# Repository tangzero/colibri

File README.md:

# colibri keyboard

## WIP ⚠️⚠️⚠️⚠️
this keyboard has not yet been tested

## Images

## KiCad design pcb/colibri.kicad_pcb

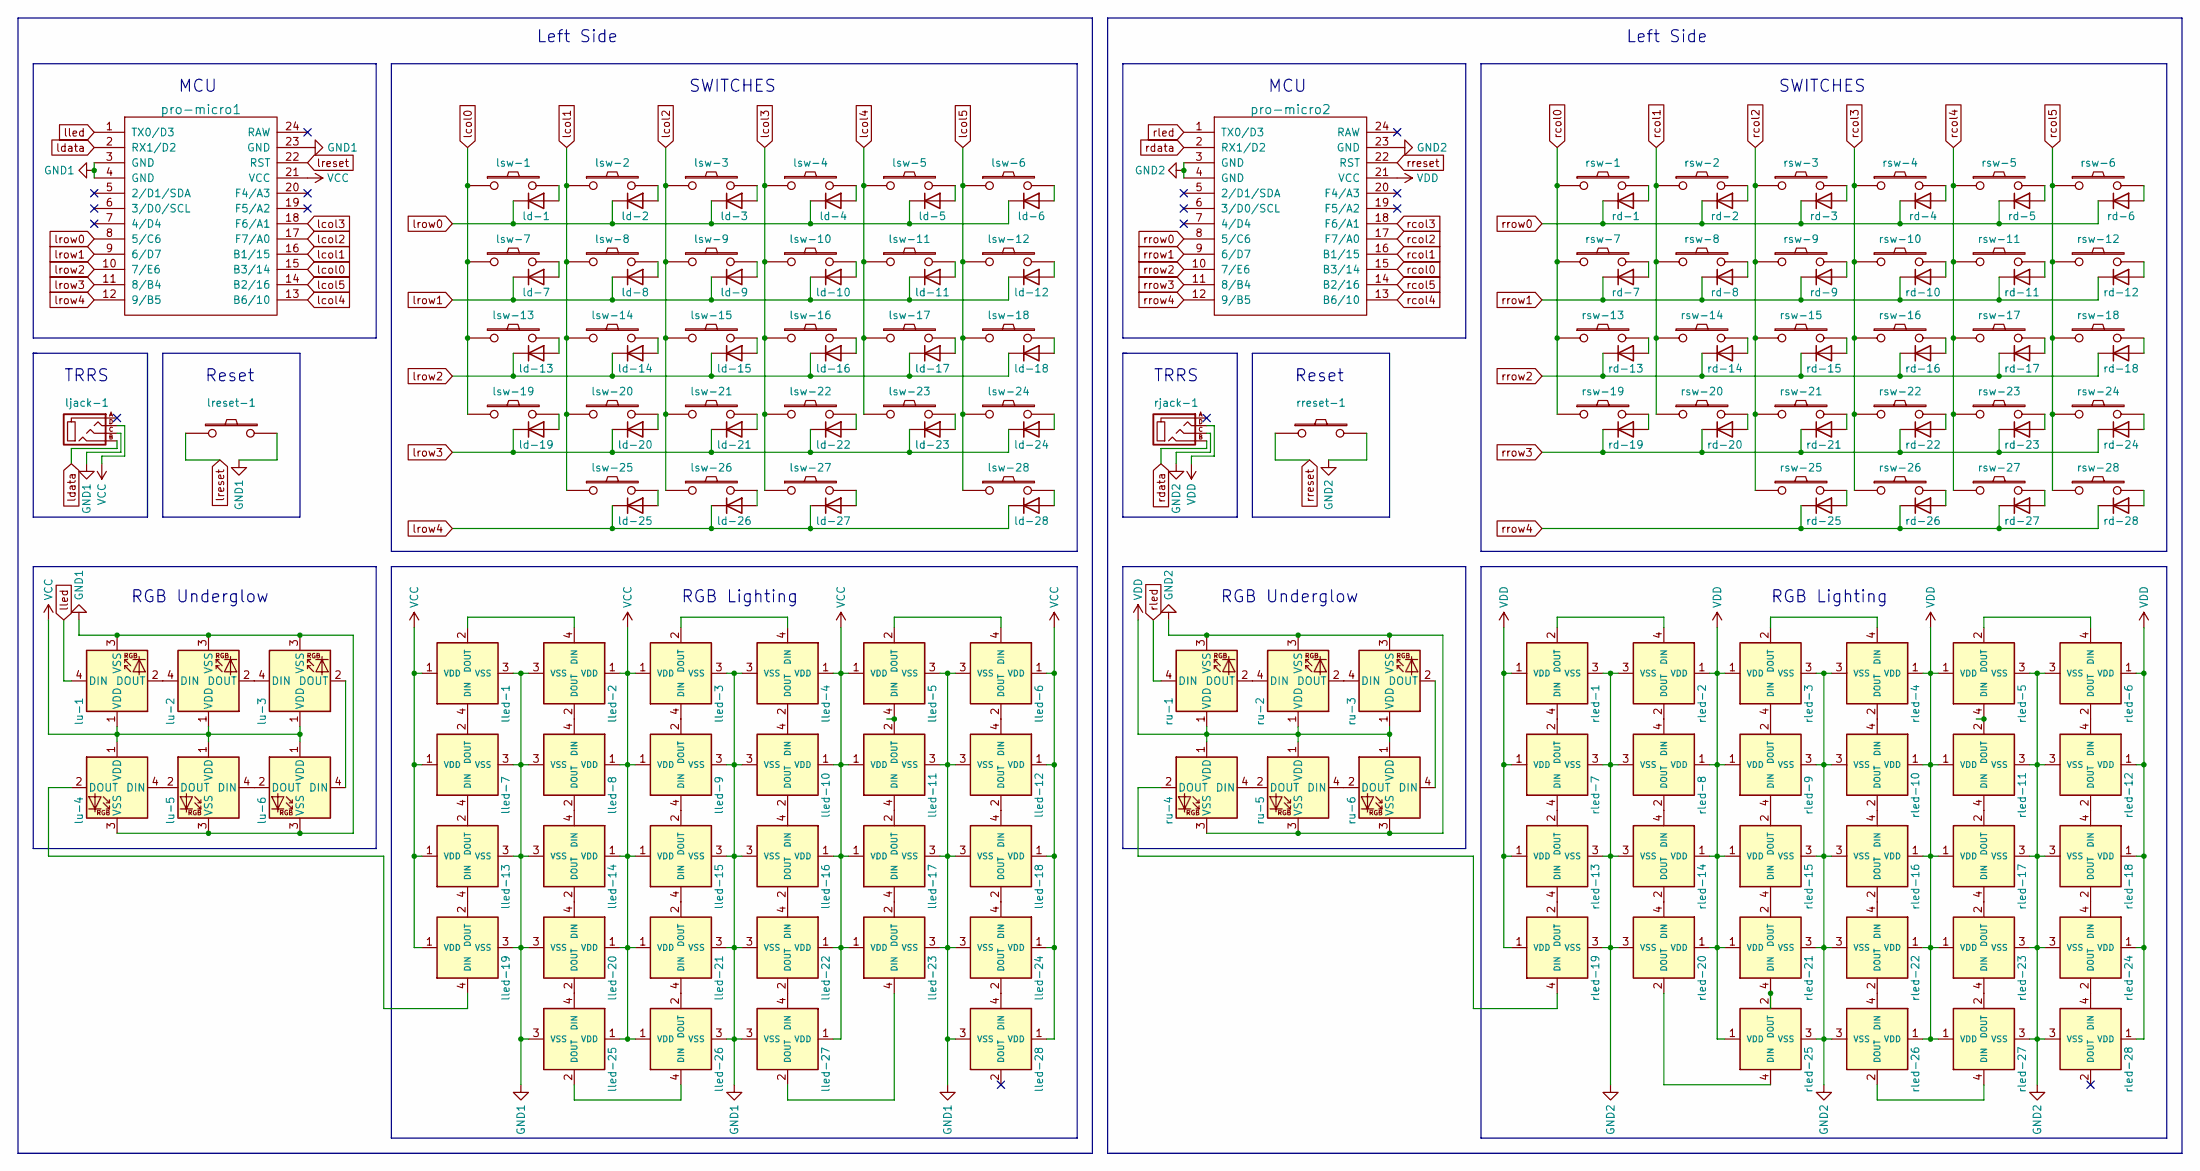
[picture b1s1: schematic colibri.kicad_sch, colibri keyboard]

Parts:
ld-1, ld-2, ld-3, ld-4, ld-5, ld-6, ld-7, ld-8, ld-9, ld-10, ld-11, ld-12, ld-13, ld-14, ld-15, ld-16, ld-17, ld-18, ld-19, ld-20, ld-21, ld-22, ld-23, ld-24, ld-25, ld-26, ld-27, ld-28: 1N4148W; D3_SMD_v2
ljack-1: MJ-4PP-9; MJ-4PP-9_1side
lled-1, lled-2, lled-3, lled-4, lled-5, lled-6, lled-7, lled-8, lled-9, lled-10, lled-11, lled-12, lled-13, lled-14, lled-15, lled-16, lled-17, lled-18, lled-19, lled-20, lled-21, lled-22, lled-23, lled-24, lled-25, lled-26, lled-27, lled-28: YS-SK6812MINI-E
lreset-1: SW_PUSH; ResetSW_4P
lsw-1, lsw-2, lsw-3, lsw-4, lsw-5, lsw-6, lsw-8, lsw-9, lsw-10, lsw-11, lsw-12, lsw-14, lsw-15, lsw-16, lsw-17, lsw-18, lsw-20, lsw-21, lsw-22, lsw-23, lsw-24: SW_PUSH; CherryMX_Hotswap
lsw-7: SW_PUSH; CherryMX_Hotswap_1.5u
lsw-13: SW_PUSH; CherryMX_Hotswap_1.75u
lsw-19: SW_PUSH; CherryMX_Hotswap_2.25u
lsw-25, lsw-26, lsw-27: SW_PUSH; CherryMX_Hotswap_1.25u
lsw-28: SW_PUSH; CherryMX_Hotswap_2u
lu-1, lu-2, lu-3, lu-4, lu-5, lu-6: WS2812B; LED_WS2812B_PLCC4_5.0x5.0mm_P3.2mm
pro-micro1, pro-micro2: ProMicro; ProMicro_v4
rd-1, rd-2, rd-3, rd-4, rd-5, rd-6, rd-7, rd-8, rd-9, rd-10, rd-11, rd-12, rd-13, rd-14, rd-15, rd-16, rd-17, rd-18, rd-19, rd-20, rd-21, rd-22, rd-23, rd-24, rd-25, rd-26, rd-27, rd-28: 1N4148W; D3_SMD_v2
rjack-1: MJ-4PP-9; MJ-4PP-9_1side
rled-1, rled-2, rled-3, rled-4, rled-5, rled-6, rled-7, rled-8, rled-9, rled-10, rled-11, rled-12, rled-13, rled-14, rled-15, rled-16, rled-17, rled-18, rled-19, rled-20, rled-21, rled-22, rled-23, rled-24, rled-25, rled-26, rled-27, rled-28: YS-SK6812MINI-E
rreset-1: SW_PUSH; ResetSW_4P
rsw-1: SW_PUSH; CherryMX_Hotswap_2u
rsw-2, rsw-3, rsw-4, rsw-5, rsw-6, rsw-8, rsw-9, rsw-10, rsw-11, rsw-12, rsw-14, rsw-15, rsw-16, rsw-17, rsw-18, rsw-20, rsw-21, rsw-22, rsw-23, rsw-24: SW_PUSH; CherryMX_Hotswap
rsw-7: SW_PUSH; CherryMX_Hotswap_1.5u
rsw-13: SW_PUSH; CherryMX_Hotswap_2.25u
rsw-19: SW_PUSH; CherryMX_Hotswap_2.75u
rsw-25, rsw-26, rsw-27, rsw-28: SW_PUSH; CherryMX_Hotswap_1.25u
ru-1, ru-2, ru-3, ru-4, ru-5, ru-6: WS2812B; LED_WS2812B_PLCC4_5.0x5.0mm_P3.2mm

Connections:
GND1: ljack-1.C, lled-1.3 (VSS), lled-2.3 (VSS), lled-3.3 (VSS), lled-4.3 (VSS), lled-5.3 (VSS), lled-6.3 (VSS), lled-7.3 (VSS), lled-8.3 (VSS), lled-9.3 (VSS), lled-10.3 (VSS), lled-11.3 (VSS), lled-12.3 (VSS), lled-13.3 (VSS), lled-14.3 (VSS), lled-15.3 (VSS), lled-16.3 (VSS), lled-17.3 (VSS), lled-18.3 (VSS), lled-19.3 (VSS), lled-20.3 (VSS), lled-21.3 (VSS), lled-22.3 (VSS), lled-23.3 (VSS), lled-24.3 (VSS), lled-25.3 (VSS), lled-26.3 (VSS), lled-27.3 (VSS), lled-28.3 (VSS), lreset-1.2, lu-1.3 (VSS), lu-2.3 (VSS), lu-3.3 (VSS), lu-4.3 (VSS), lu-5.3 (VSS), lu-6.3 (VSS), pro-micro1.3 (GND), pro-micro1.4 (GND), pro-micro1.23 (GND)
GND2: pro-micro2.3 (GND), pro-micro2.4 (GND), pro-micro2.23 (GND), rjack-1.C, rled-1.3 (VSS), rled-2.3 (VSS), rled-3.3 (VSS), rled-4.3 (VSS), rled-5.3 (VSS), rled-6.3 (VSS), rled-7.3 (VSS), rled-8.3 (VSS), rled-9.3 (VSS), rled-10.3 (VSS), rled-11.3 (VSS), rled-12.3 (VSS), rled-13.3 (VSS), rled-14.3 (VSS), rled-15.3 (VSS), rled-16.3 (VSS), rled-17.3 (VSS), rled-18.3 (VSS), rled-19.3 (VSS), rled-20.3 (VSS), rled-21.3 (VSS), rled-22.3 (VSS), rled-23.3 (VSS), rled-24.3 (VSS), rled-25.3 (VSS), rled-26.3 (VSS), rled-27.3 (VSS), rled-28.3 (VSS), rreset-1.2, ru-1.3 (VSS), ru-2.3 (VSS), ru-3.3 (VSS), ru-4.3 (VSS), ru-5.3 (VSS), ru-6.3 (VSS)
unnamed: ld-1.2 (A), lsw-1.2
unnamed: ld-2.2 (A), lsw-2.2
unnamed: ld-3.2 (A), lsw-3.2
unnamed: ld-4.2 (A), lsw-4.2
unnamed: ld-5.2 (A), lsw-5.2
unnamed: ld-6.2 (A), lsw-6.2
unnamed: ld-7.2 (A), lsw-7.2
unnamed: ld-8.2 (A), lsw-8.2
unnamed: ld-9.2 (A), lsw-9.2
unnamed: ld-10.2 (A), lsw-10.2
unnamed: ld-11.2 (A), lsw-11.2
unnamed: ld-12.2 (A), lsw-12.2
unnamed: ld-13.2 (A), lsw-13.2
unnamed: ld-14.2 (A), lsw-14.2
unnamed: ld-15.2 (A), lsw-15.2
unnamed: ld-16.2 (A), lsw-16.2
unnamed: ld-17.2 (A), lsw-17.2
unnamed: ld-18.2 (A), lsw-18.2
unnamed: ld-19.2 (A), lsw-19.2
unnamed: ld-20.2 (A), lsw-20.2
unnamed: ld-21.2 (A), lsw-21.2
unnamed: ld-22.2 (A), lsw-22.2
unnamed: ld-23.2 (A), lsw-23.2
unnamed: ld-24.2 (A), lsw-24.2
unnamed: ld-25.2 (A), lsw-25.2
unnamed: ld-26.2 (A), lsw-26.2
unnamed: ld-27.2 (A), lsw-27.2
unnamed: ld-28.2 (A), lsw-28.2
unnamed: lled-1.2 (DOUT), lled-2.4 (DIN)
unnamed: lled-1.4 (DIN), lled-7.2 (DOUT)
unnamed: lled-2.2 (DOUT), lled-8.4 (DIN)
unnamed: lled-3.2 (DOUT), lled-4.4 (DIN)
unnamed: lled-3.4 (DIN), lled-9.2 (DOUT)
unnamed: lled-5.2 (DOUT), lled-6.4 (DIN)
unnamed: lled-10.2 (DOUT), lled-16.4 (DIN)
unnamed: lled-4.2 (DOUT), lled-10.4 (DIN)
unnamed: lled-5.4 (DIN), lled-11.2 (DOUT)
unnamed: lled-11.4 (DIN), lled-17.2 (DOUT)
unnamed: lled-12.2 (DOUT), lled-18.4 (DIN)
unnamed: lled-6.2 (DOUT), lled-12.4 (DIN)
unnamed: lled-7.4 (DIN), lled-13.2 (DOUT)
unnamed: lled-13.4 (DIN), lled-19.2 (DOUT)
unnamed: lled-14.2 (DOUT), lled-20.4 (DIN)
unnamed: lled-8.2 (DOUT), lled-14.4 (DIN)
unnamed: lled-9.4 (DIN), lled-15.2 (DOUT)
unnamed: lled-15.4 (DIN), lled-21.2 (DOUT)
unnamed: lled-16.2 (DOUT), lled-22.4 (DIN)
unnamed: lled-17.4 (DIN), lled-23.2 (DOUT)
unnamed: lled-18.2 (DOUT), lled-24.4 (DIN)
unnamed: lled-19.4 (DIN), lu-4.2 (DOUT)
unnamed: lled-20.2 (DOUT), lled-25.4 (DIN)
unnamed: lled-21.4 (DIN), lled-26.2 (DOUT)
unnamed: lled-22.2 (DOUT), lled-27.4 (DIN)
unnamed: lled-23.4 (DIN), lled-27.2 (DOUT)
unnamed: lled-24.2 (DOUT), lled-28.4 (DIN)
unnamed: lled-25.2 (DOUT), lled-26.4 (DIN)
unnamed: lu-1.2 (DOUT), lu-2.4 (DIN)
unnamed: lu-2.2 (DOUT), lu-3.4 (DIN)
unnamed: lu-3.2 (DOUT), lu-6.4 (DIN)
unnamed: lu-4.4 (DIN), lu-5.2 (DOUT)
unnamed: lu-5.4 (DIN), lu-6.2 (DOUT)
unnamed: rd-1.2 (A), rsw-1.2
unnamed: rd-2.2 (A), rsw-2.2
unnamed: rd-3.2 (A), rsw-3.2
unnamed: rd-4.2 (A), rsw-4.2
unnamed: rd-5.2 (A), rsw-5.2
unnamed: rd-6.2 (A), rsw-6.2
unnamed: rd-7.2 (A), rsw-7.2
unnamed: rd-8.2 (A), rsw-8.2
unnamed: rd-9.2 (A), rsw-9.2
unnamed: rd-10.2 (A), rsw-10.2
unnamed: rd-11.2 (A), rsw-11.2
unnamed: rd-12.2 (A), rsw-12.2
unnamed: rd-13.2 (A), rsw-13.2
unnamed: rd-14.2 (A), rsw-14.2
unnamed: rd-15.2 (A), rsw-15.2
unnamed: rd-16.2 (A), rsw-16.2
unnamed: rd-17.2 (A), rsw-17.2
unnamed: rd-18.2 (A), rsw-18.2
unnamed: rd-19.2 (A), rsw-19.2
unnamed: rd-20.2 (A), rsw-20.2
unnamed: rd-21.2 (A), rsw-21.2
unnamed: rd-22.2 (A), rsw-22.2
unnamed: rd-23.2 (A), rsw-23.2
unnamed: rd-24.2 (A), rsw-24.2
unnamed: rd-25.2 (A), rsw-25.2
unnamed: rd-26.2 (A), rsw-26.2
unnamed: rd-27.2 (A), rsw-27.2
unnamed: rd-28.2 (A), rsw-28.2
unnamed: rled-1.2 (DOUT), rled-2.4 (DIN)
unnamed: rled-1.4 (DIN), rled-7.2 (DOUT)
unnamed: rled-2.2 (DOUT), rled-8.4 (DIN)
unnamed: rled-3.2 (DOUT), rled-4.4 (DIN)
unnamed: rled-3.4 (DIN), rled-9.2 (DOUT)
unnamed: rled-5.2 (DOUT), rled-6.4 (DIN)
unnamed: rled-10.2 (DOUT), rled-16.4 (DIN)
unnamed: rled-4.2 (DOUT), rled-10.4 (DIN)
unnamed: rled-5.4 (DIN), rled-11.2 (DOUT)
unnamed: rled-11.4 (DIN), rled-17.2 (DOUT)
unnamed: rled-12.2 (DOUT), rled-18.4 (DIN)
unnamed: rled-6.2 (DOUT), rled-12.4 (DIN)
unnamed: rled-7.4 (DIN), rled-13.2 (DOUT)
unnamed: rled-13.4 (DIN), rled-19.2 (DOUT)
unnamed: rled-14.2 (DOUT), rled-20.4 (DIN)
unnamed: rled-8.2 (DOUT), rled-14.4 (DIN)
unnamed: rled-9.4 (DIN), rled-15.2 (DOUT)
unnamed: rled-15.4 (DIN), rled-21.2 (DOUT)
unnamed: rled-16.2 (DOUT), rled-22.4 (DIN)
unnamed: rled-17.4 (DIN), rled-23.2 (DOUT)
unnamed: rled-18.2 (DOUT), rled-24.4 (DIN)
unnamed: rled-19.4 (DIN), ru-4.2 (DOUT)
unnamed: rled-20.2 (DOUT), rled-25.4 (DIN)
unnamed: rled-21.4 (DIN), rled-25.2 (DOUT)
unnamed: rled-22.2 (DOUT), rled-26.4 (DIN)
unnamed: rled-23.4 (DIN), rled-27.2 (DOUT)
unnamed: rled-24.2 (DOUT), rled-28.4 (DIN)
unnamed: rled-26.2 (DOUT), rled-27.4 (DIN)
unnamed: ru-1.2 (DOUT), ru-2.4 (DIN)
unnamed: ru-2.2 (DOUT), ru-3.4 (DIN)
unnamed: ru-3.2 (DOUT), ru-6.4 (DIN)
unnamed: ru-4.4 (DIN), ru-5.2 (DOUT)
unnamed: ru-5.4 (DIN), ru-6.2 (DOUT)
VCC: ljack-1.D, lled-1.1 (VDD), lled-2.1 (VDD), lled-3.1 (VDD), lled-4.1 (VDD), lled-5.1 (VDD), lled-6.1 (VDD), lled-7.1 (VDD), lled-8.1 (VDD), lled-9.1 (VDD), lled-10.1 (VDD), lled-11.1 (VDD), lled-12.1 (VDD), lled-13.1 (VDD), lled-14.1 (VDD), lled-15.1 (VDD), lled-16.1 (VDD), lled-17.1 (VDD), lled-18.1 (VDD), lled-19.1 (VDD), lled-20.1 (VDD), lled-21.1 (VDD), lled-22.1 (VDD), lled-23.1 (VDD), lled-24.1 (VDD), lled-25.1 (VDD), lled-26.1 (VDD), lled-27.1 (VDD), lled-28.1 (VDD), lu-1.1 (VDD), lu-2.1 (VDD), lu-3.1 (VDD), lu-4.1 (VDD), lu-5.1 (VDD), lu-6.1 (VDD), pro-micro1.21 (VCC)
VDD: pro-micro2.21 (VCC), rjack-1.D, rled-1.1 (VDD), rled-2.1 (VDD), rled-3.1 (VDD), rled-4.1 (VDD), rled-5.1 (VDD), rled-6.1 (VDD), rled-7.1 (VDD), rled-8.1 (VDD), rled-9.1 (VDD), rled-10.1 (VDD), rled-11.1 (VDD), rled-12.1 (VDD), rled-13.1 (VDD), rled-14.1 (VDD), rled-15.1 (VDD), rled-16.1 (VDD), rled-17.1 (VDD), rled-18.1 (VDD), rled-19.1 (VDD), rled-20.1 (VDD), rled-21.1 (VDD), rled-22.1 (VDD), rled-23.1 (VDD), rled-24.1 (VDD), rled-25.1 (VDD), rled-26.1 (VDD), rled-27.1 (VDD), rled-28.1 (VDD), ru-1.1 (VDD), ru-2.1 (VDD), ru-3.1 (VDD), ru-4.1 (VDD), ru-5.1 (VDD), ru-6.1 (VDD)
lcol0: lsw-1.1, lsw-7.1, lsw-13.1, lsw-19.1, pro-micro1.15 (B3/14)
lcol1: lsw-2.1, lsw-8.1, lsw-14.1, lsw-20.1, lsw-25.1, pro-micro1.16 (B1/15)
lcol2: lsw-3.1, lsw-9.1, lsw-15.1, lsw-21.1, lsw-26.1, pro-micro1.17 (F7/A0)
lcol3: lsw-4.1, lsw-10.1, lsw-16.1, lsw-22.1, lsw-27.1, pro-micro1.18 (F6/A1)
lcol4: lsw-5.1, lsw-11.1, lsw-17.1, lsw-23.1, pro-micro1.13 (B6/10)
lcol5: lsw-6.1, lsw-12.1, lsw-18.1, lsw-24.1, lsw-28.1, pro-micro1.14 (B2/16)
ldata: ljack-1.B, pro-micro1.2 (RX1/D2)
lled: lu-1.4 (DIN), pro-micro1.1 (TX0/D3)
lreset: lreset-1.1, pro-micro1.22 (RST)
lrow0: ld-1.1 (K), ld-2.1 (K), ld-3.1 (K), ld-4.1 (K), ld-5.1 (K), ld-6.1 (K), pro-micro1.8 (5/C6)
lrow1: ld-7.1 (K), ld-8.1 (K), ld-9.1 (K), ld-10.1 (K), ld-11.1 (K), ld-12.1 (K), pro-micro1.9 (6/D7)
lrow2: ld-13.1 (K), ld-14.1 (K), ld-15.1 (K), ld-16.1 (K), ld-17.1 (K), ld-18.1 (K), pro-micro1.10 (7/E6)
lrow3: ld-19.1 (K), ld-20.1 (K), ld-21.1 (K), ld-22.1 (K), ld-23.1 (K), ld-24.1 (K), pro-micro1.11 (8/B4)
lrow4: ld-25.1 (K), ld-26.1 (K), ld-27.1 (K), ld-28.1 (K), pro-micro1.12 (9/B5)
rcol0: pro-micro2.15 (B3/14), rsw-1.1, rsw-7.1, rsw-13.1, rsw-19.1
rcol1: pro-micro2.16 (B1/15), rsw-2.1, rsw-8.1, rsw-14.1, rsw-20.1
rcol2: pro-micro2.17 (F7/A0), rsw-3.1, rsw-9.1, rsw-15.1, rsw-21.1, rsw-25.1
rcol3: pro-micro2.18 (F6/A1), rsw-4.1, rsw-10.1, rsw-16.1, rsw-22.1, rsw-26.1
rcol4: pro-micro2.13 (B6/10), rsw-5.1, rsw-11.1, rsw-17.1, rsw-23.1, rsw-27.1
rcol5: pro-micro2.14 (B2/16), rsw-6.1, rsw-12.1, rsw-18.1, rsw-24.1, rsw-28.1
rdata: pro-micro2.2 (RX1/D2), rjack-1.B
rled: pro-micro2.1 (TX0/D3), ru-1.4 (DIN)
rreset: pro-micro2.22 (RST), rreset-1.1
rrow0: pro-micro2.8 (5/C6), rd-1.1 (K), rd-2.1 (K), rd-3.1 (K), rd-4.1 (K), rd-5.1 (K), rd-6.1 (K)
rrow1: pro-micro2.9 (6/D7), rd-7.1 (K), rd-8.1 (K), rd-9.1 (K), rd-10.1 (K), rd-11.1 (K), rd-12.1 (K)
rrow2: pro-micro2.10 (7/E6), rd-13.1 (K), rd-14.1 (K), rd-15.1 (K), rd-16.1 (K), rd-17.1 (K), rd-18.1 (K)
rrow3: pro-micro2.11 (8/B4), rd-19.1 (K), rd-20.1 (K), rd-21.1 (K), rd-22.1 (K), rd-23.1 (K), rd-24.1 (K)
rrow4: pro-micro2.12 (9/B5), rd-25.1 (K), rd-26.1 (K), rd-27.1 (K), rd-28.1 (K)

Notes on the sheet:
TRRS
RGB Lighting
MCU
Left Side
RGB Underglow
SWITCHES
Reset

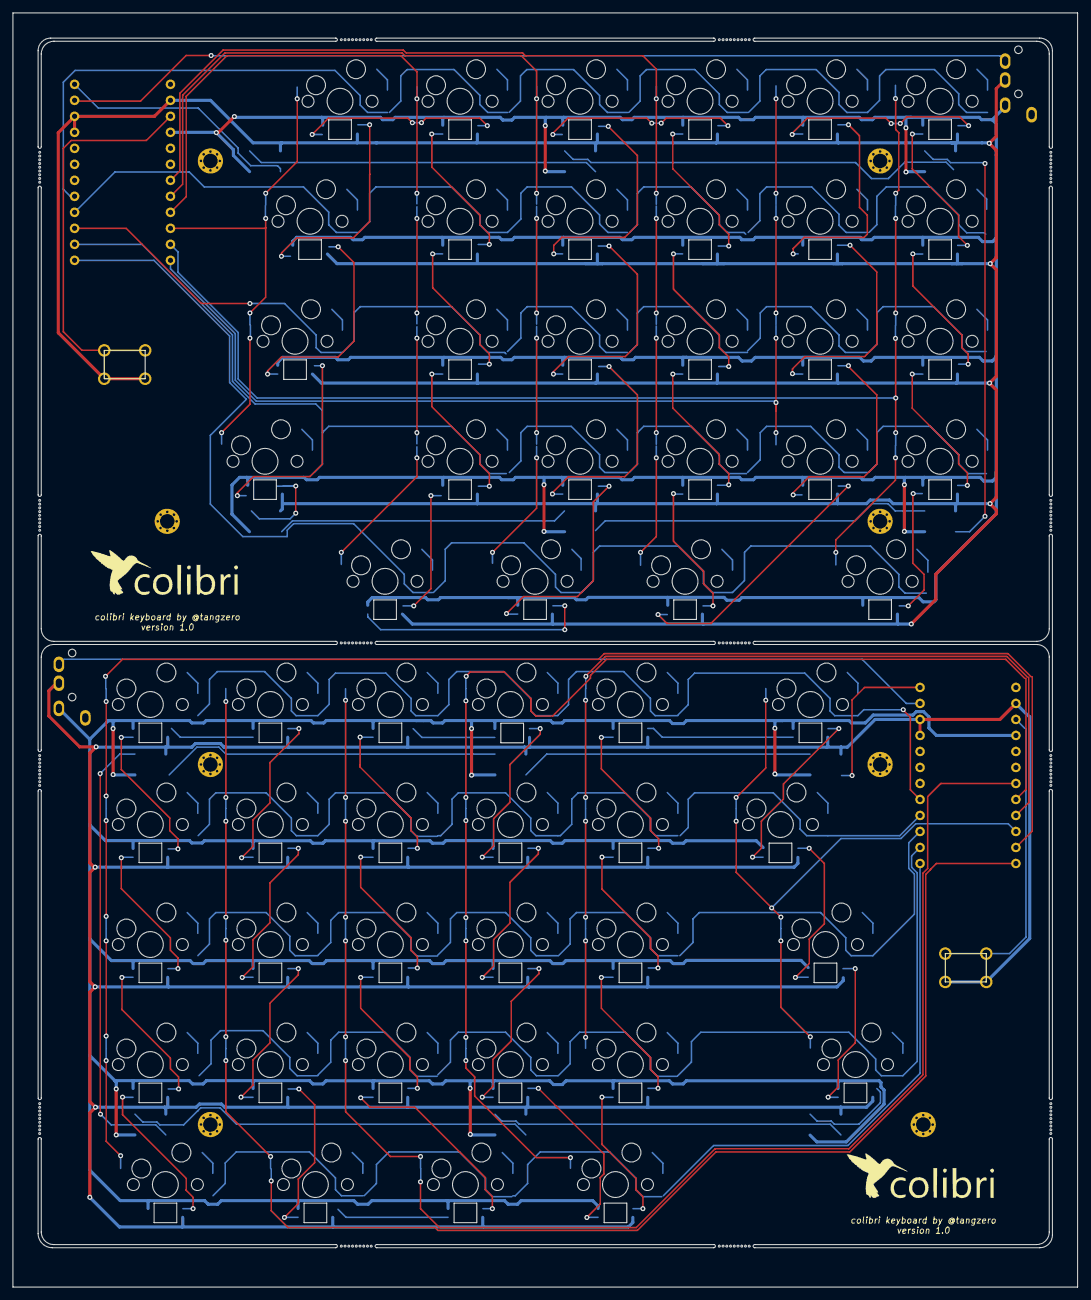
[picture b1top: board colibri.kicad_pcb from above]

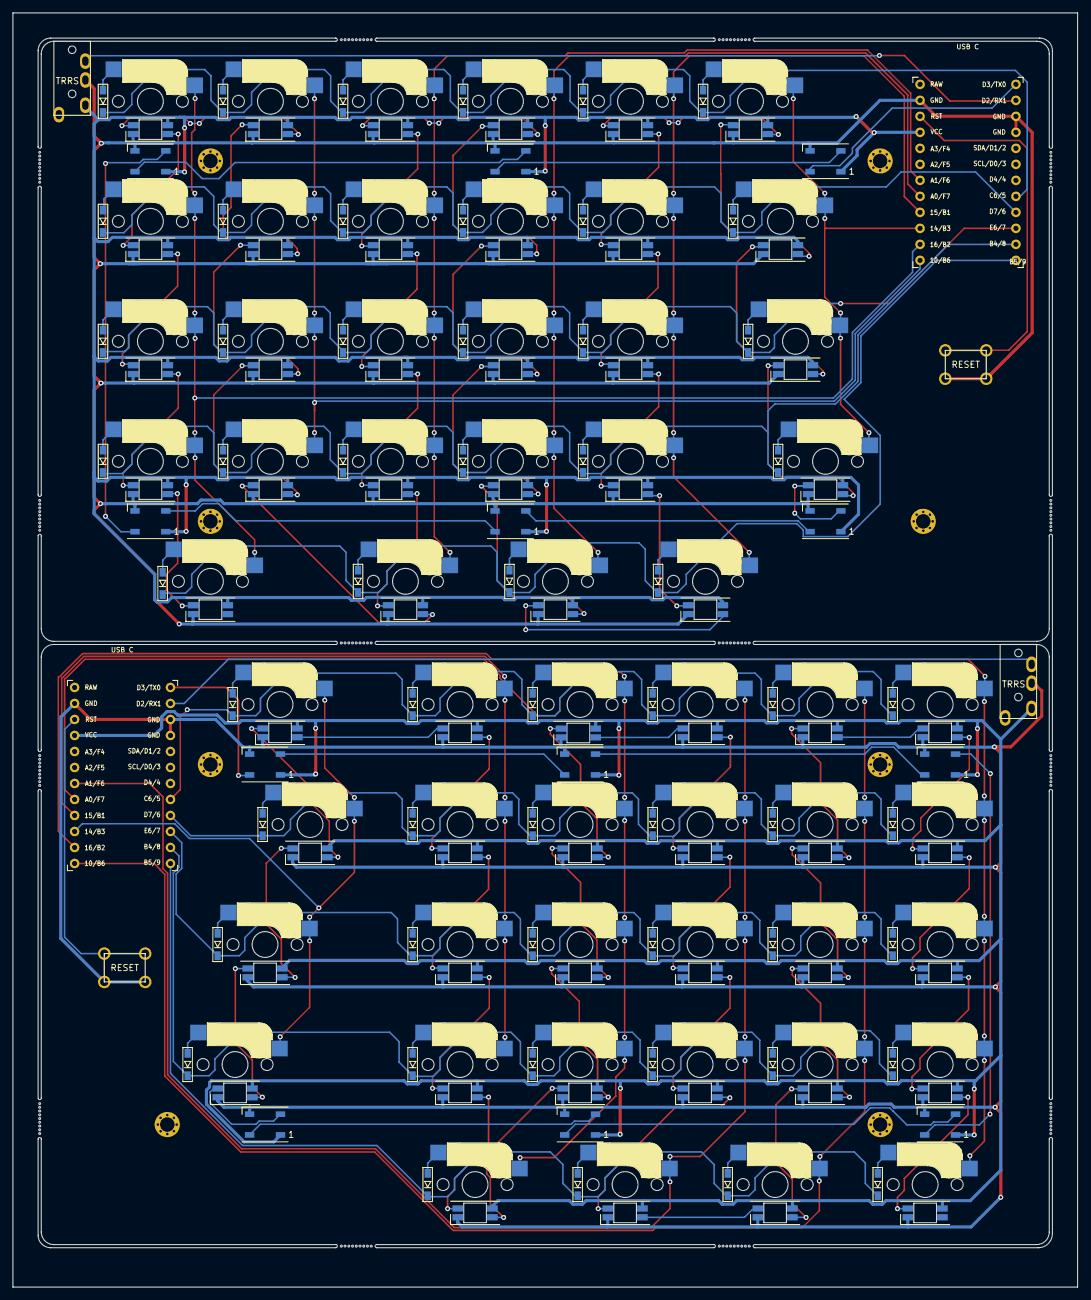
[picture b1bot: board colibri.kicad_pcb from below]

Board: 2 copper layers, 169.0 x 202.2 mm, 194 parts (130 on the bottom side), 154 nets.

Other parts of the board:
Ref**: Val**; M2_HOLE_v3
Ref**#2, Ref**#3, Ref**#4, Ref**#5, Ref**#6, Ref**#7, Ref**#8: Val**; M2_HOLE_v3

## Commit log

2023-01-26 playing around with footprints
2023-01-26 basic layout
2023-01-26 diodes on place
2023-01-26 schematics almost finished for left side
2023-01-26 better LED placement
2023-01-26 LEDs placed on the PCB
2023-01-26 better keyboard layout
2023-01-26 board size
2023-01-27 rows connected
2023-01-27 columns connected
2023-01-27 better connections
2023-01-27 added missing column
2023-01-27 connecting leds
2023-01-27 all leds connected
2023-01-27 all keys connected
2023-01-27 added some M2 mounting holes
2023-01-27 TRRS jack in place
2023-01-27 better component placement + more M2 holes
2023-01-27 reset button
2023-01-27 some images
2023-01-27 starting to build the right side
2023-01-28 fix gnd and vcc symbols for left side
2023-01-28 added one more key to the right side
2023-01-28 fixed gnd and vcc width for left side pcb
2023-01-28 all components placed on the right position
2023-01-29 rows connected on the right side
2023-01-29 right side done
2023-01-29 new images
2023-01-29 colibri logo
2023-01-29 added colibri logo
2023-01-29 version 1.0
